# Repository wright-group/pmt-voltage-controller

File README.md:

# pmt-voltage-controller

ABANDONED

A simple interface designed to endow PMT drivers with computer control.
Effectively this a USB interface to a single analog and single TTL output.

## Repository

This is an open source hardware project licensed under the CERN Open Hardware Licence Version 2 - Permissive.
Please see the LICENSE file for the complete license.

## PCB

This PCB was designed using KiCAD version 5.
Refer to `pmt-control.pdf` for schematic.
PCB images generated with [tracespace](https://github.com/tracespace/tracespace) follow.

## Bill of Materials

| reference      | value         | manufacturer  | part number          | vendors |
| :------------- | :------------ | :------------ | :------------------- | :------ |

## Firmware

### Photon Technology 914

PMT voltage controlled by a 0 to +5 V input on the High Voltage control line corresponding to 9 to -1250 V on the PMT.

### Hamamatsu M901X

PMT voltage controlled by a 0 to 900 mV input.

## Changelog

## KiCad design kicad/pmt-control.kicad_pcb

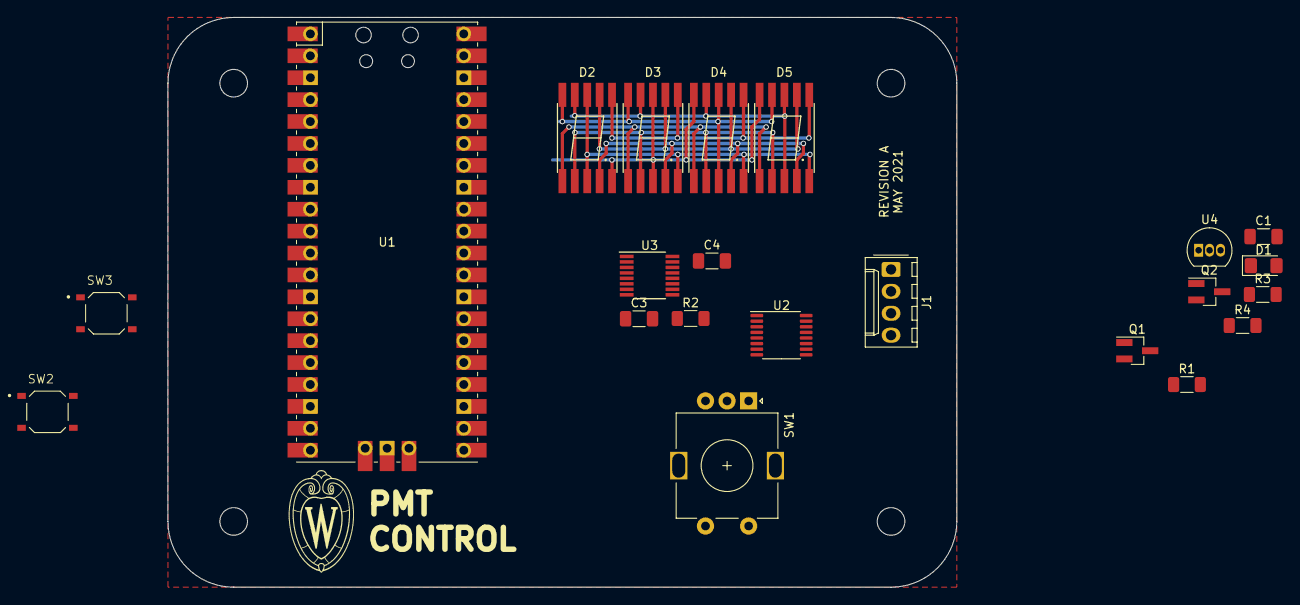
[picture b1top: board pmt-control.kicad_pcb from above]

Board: 2 copper layers, 91.4 x 66.0 mm, 22 parts (0 on the bottom side), 32 nets.

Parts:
C1: 100nF; C_1206_3216Metric_Pad1.33x1.80mm_HandSolder
C3: C; C_1206_3216Metric_Pad1.33x1.80mm_HandSolder
C4: 100n; C_1206_3216Metric_Pad1.33x1.80mm_HandSolder
D1: LED; LED_1206_3216Metric_Pad1.42x1.75mm_HandSolder
D2, D3, D4, D5: ACSC02-41SURKWA-F01
J1: OUT; Molex_KK-254_AE-6410-04A_1x04_P2.54mm_Vertical
Q1, Q2: 2N7000; SOT-23_Handsoldering
R1, R2, R3, R4: R_US; R_1206_3216Metric_Pad1.30x1.75mm_HandSolder
SW1: Rotary_Encoder_Switch; RotaryEncoder_Alps_EC11E-Switch_Vertical_H20mm
SW2: TTL; SW_PTS526_SM08_SMTR2_LFS
SW3: RST; SW_PTS526_SM08_SMTR2_LFS
U1: Pico; RPi_Pico_SMD_TH
U2: AD5761BRUZ-AD5761BRUZ; TSSOP-16_4.4x5mm_P0.65mm
U3: MAX6951; QSOP-16_3.9x4.9mm_P0.635mm
U4: LM285Z-2.5; TO-92_Inline

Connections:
+3V3: C4.1, U1.36, U2.15, U3.16
+5V: C1.1, J1.4, R1.1, R3.1, R4.1, U1.40, U2.8
/7seg/SEG0: D2.3, D2.8, D3.5, D4.5, D5.5, U3.6
/7seg/SEG1: D2.5, D3.3, D3.8, D4.10, D5.10, U3.5
/7seg/SEG2: D2.10, D3.10, D4.3, D4.8, D5.9, U3.4
/7seg/SEG3: D2.9, D3.9, D4.9, D5.3, D5.8, U3.3
/7seg/SEG4: D2.1, D3.1, D4.1, D5.1, U3.14
/7seg/SEG5: D2.2, D3.2, D4.2, D5.2, U3.13
/7seg/SEG6: D2.4, D3.4, D4.4, D5.4, U3.12
/7seg/SEG7: D2.6, D3.6, D4.6, D5.6, U3.11
/7seg/SEG8: D2.7, D3.7, D4.7, D5.7, U3.10
/7seg/~CS~: U1.26, U3.15
GND: C1.2, C3.2, C4.2, J1.1, Q1.2, Q2.2, R2.2, SW1.C, SW2.1, SW3.2, U1.3, U1.8, U1.13, U1.18, U1.23, U1.28, U1.38, U1.42, U2.5, U2.6, U2.11, U2.16, U3.8, U4.3
MISO: U1.21, U2.10
MOSI: U1.25, U2.12, U3.1
unnamed: C3.1, U3.9
unnamed: D1.1, Q1.3
unnamed: D1.2, R3.2
unnamed: J1.2, Q2.3, R4.2
unnamed: J1.3, U2.7
unnamed: Q1.1, Q2.1, U1.27
unnamed: R1.2, U2.4, U4.2
unnamed: R2.1, U3.7
unnamed: SW1.A, U1.19
unnamed: SW1.B, U1.20
unnamed: SW2.2, U1.9
unnamed: SW3.1, U1.30
unnamed: U1.4, U2.13
unnamed: U1.5, U2.1
unnamed: U1.6, U2.2
unnamed: U1.7, U2.3
SCK: U1.24, U2.14, U3.2

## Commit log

2021-05-17 copy paste
2021-05-25 schematic
2021-10-13 from leo
